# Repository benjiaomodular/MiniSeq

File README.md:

# MiniSeq
[![CC BY-SA 4.0][cc-by-sa-shield]][cc-by-sa]

Full docs on my website: https://benjiaomodular.com/post/miniseq/

This is my second time building a Baby-8 step CV sequencer since my [plexiglass Baby-8 build](https://benjiaomodular.com/post/2021-04-09-8-step-sequencer) from two years ago. This, time I added a gate output, a reset input, and a step length control.

## Schematics

## License

This work is licensed under a
[Creative Commons Attribution-ShareAlike 4.0 International License][cc-by-sa].

[![CC BY-SA 4.0][cc-by-sa-image]][cc-by-sa]

[cc-by-sa]: http://creativecommons.org/licenses/by-sa/4.0/
[cc-by-sa-image]: https://licensebuttons.net/l/by-sa/4.0/88x31.png
[cc-by-sa-shield]: https://img.shields.io/badge/License-CC%20BY--SA%204.0-lightgrey.svg

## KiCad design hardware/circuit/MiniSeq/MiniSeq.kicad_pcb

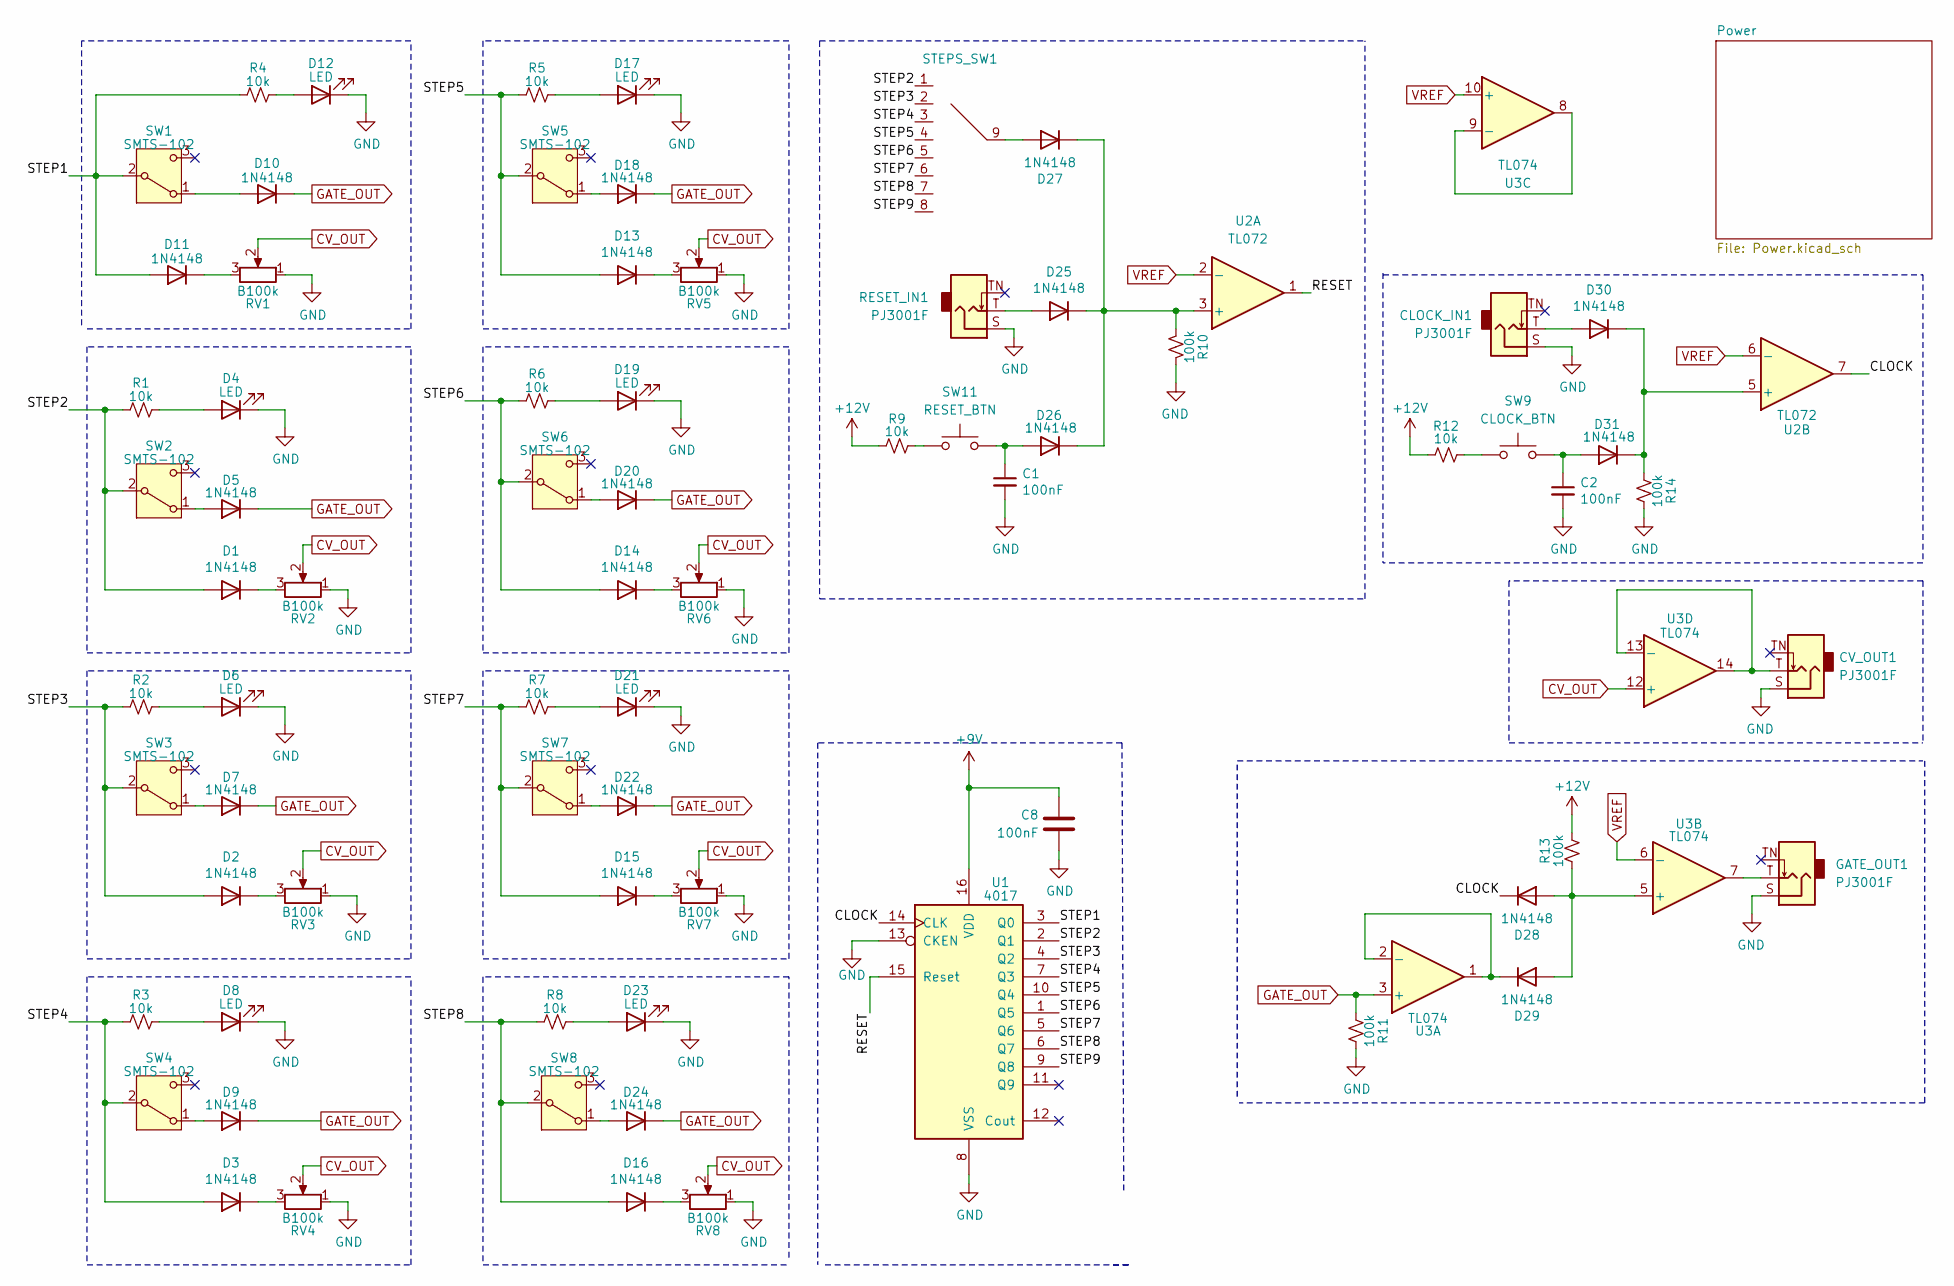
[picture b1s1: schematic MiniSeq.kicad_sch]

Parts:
C1, C2: 100nF; C_0805_2012Metric_Pad1.18x1.45mm_HandSolder; Manufacturers Part Numb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 CC0805KRX7R9BB104
C8: 100nF; C_0805_2012Metric_Pad1.18x1.45mm_HandSolder
CLOCK_IN1: PJ3001F; AudioJack_3.5mm; Manufacturers Part Numb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 PJ-3001F
CV_OUT1: PJ3001F; AudioJack_3.5mm; Manufacturers Part Numb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 PJ-3001F
D1, D2, D3, D5, D7, D9, D10, D11, D13, D14, D15, D16, D18, D20, D22, D24, D25, D26, D27, D28, D29, D30, D31: 1N4148; D_SOD-123; Manufacturers Part Numb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 1N4148WQ-7-F
D4, D6, D8, D12, D17, D19, D21, D23: LED; LED_D3.0mm
GATE_OUT1: PJ3001F; AudioJack_3.5mm; Manufacturers Part Numb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 PJ-3001F
R1, R2, R3, R4, R5, R6, R7, R8, R9, R12: 10k; R_0603_1608Metric_Pad0.98x0.95mm_HandSolder; Manufacturers Part Numb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 AC0603FR-0710KL
R10, R11, R13, R14: 100k; R_0603_1608Metric_Pad0.98x0.95mm_HandSolder; Manufacturers Part Numb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 RC0603FR-07100KL
RESET_IN1: PJ3001F; AudioJack_3.5mm; Manufacturers Part Numb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 PJ-3001F
RV1, RV2, RV3, RV4, RV5, RV6, RV7, RV8: B100k; Potentiometer_RV09; Manufacturers Part Numb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 RD901F-40-15R1-B100K
STEPS_SW1: RotarySwitch_SR16_POLE1_WAY8
SW1, SW2, SW3, SW4, SW5, SW6, SW7, SW8: SMTS-102; ToggleSwitch_SMTS-102; Manufacturers Part Numb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 SMTS-201
SW9: CLOCK_BTN; SW_Cherry_MX_1.00u_PCB
SW11: RESET_BTN; SW_Cherry_MX_1.00u_PCB
U1: 4017; SOIC-16W_5.3x10.2mm_P1.27mm; Manufacturers Part Numb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 CD40174BM96
U2: TL072; SOIC-8_3.9x4.9mm_P1.27mm; Manufacturers Part Numb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 TL072CDT
U3: TL074; SOIC-14_3.9x8.7mm_P1.27mm; Manufacturers Part Numb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 TL074ACDT

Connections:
+9V: C8.1, U1.16 (VDD); also elsewhere on the board
+12V: R9.2, R12.2, R13.1; also elsewhere on the board
/CLOCK: D28.1 (K), U1.14 (CLK), U2.7
/RESET: U1.15 (Reset), U2.1
/STEP1: D11.2 (A), R4.2, SW1.2 (B), U1.3 (Q0)
/STEP2: D1.2 (A), R1.2, STEPS_SW1.1, SW2.2 (B), U1.2 (Q1)
/STEP3: D2.2 (A), R2.2, STEPS_SW1.2, SW3.2 (B), U1.4 (Q2)
/STEP4: D3.2 (A), R3.2, STEPS_SW1.3, SW4.2 (B), U1.7 (Q3)
/STEP5: D13.2 (A), R5.2, STEPS_SW1.4, SW5.2 (B), U1.10 (Q4)
/STEP6: D14.2 (A), R6.2, STEPS_SW1.5, SW6.2 (B), U1.1 (Q5)
/STEP7: D15.2 (A), R7.2, STEPS_SW1.6, SW7.2 (B), U1.5 (Q6)
/STEP8: D16.2 (A), R8.2, STEPS_SW1.7, SW8.2 (B), U1.6 (Q7)
/STEP9: STEPS_SW1.8, U1.9 (Q8)
CV_OUT: RV1.2, RV2.2, RV3.2, RV4.2, RV5.2, RV6.2, RV7.2, RV8.2, U3.12 (+)
GATE_OUT: D5.1 (K), D7.1 (K), D9.1 (K), D10.1 (K), D18.1 (K), D20.1 (K), D22.1 (K), D24.1 (K), R11.2, U3.3 (+)
GND: C1.2, C2.2, C8.2, CLOCK_IN1.S, CV_OUT1.S, D4.1 (K), D6.1 (K), D8.1 (K), D12.1 (K), D17.1 (K), D19.1 (K), D21.1 (K), D23.1 (K), GATE_OUT1.S, R10.2, R11.1, R14.1, RESET_IN1.S, RV1.1, RV2.1, RV3.1, RV4.1, RV5.1, RV6.1, RV7.1, RV8.1, U1.8 (VSS), U1.13 (CKEN); also elsewhere on the board
unnamed: D1.1 (K), RV2.3
unnamed: D2.1 (K), RV3.3
unnamed: D3.1 (K), RV4.3
unnamed: D4.2 (A), R1.1
unnamed: D5.2 (A), SW2.1 (A)
unnamed: D6.2 (A), R2.1
unnamed: D7.2 (A), SW3.1 (A)
unnamed: D8.2 (A), R3.1
unnamed: D9.2 (A), SW4.1 (A)
unnamed: D10.2 (A), SW1.1 (A)
unnamed: D11.1 (K), RV1.3
unnamed: D12.2 (A), R4.1
unnamed: D13.1 (K), RV5.3
unnamed: D14.1 (K), RV6.3
unnamed: D15.1 (K), RV7.3
unnamed: D16.1 (K), RV8.3
unnamed: D17.2 (A), R5.1
unnamed: D18.2 (A), SW5.1 (A)
unnamed: D19.2 (A), R6.1
unnamed: D20.2 (A), SW6.1 (A)
unnamed: D21.2 (A), R7.1
unnamed: D22.2 (A), SW7.1 (A)
unnamed: D23.2 (A), R8.1
unnamed: D24.2 (A), SW8.1 (A)
unnamed: D25.2 (A), RESET_IN1.T
unnamed: D25.1 (K), D26.1 (K), D27.1 (K), R10.1, U2.3 (+)
unnamed: C1.1, D26.2 (A), SW11.2
unnamed: D27.2 (A), STEPS_SW1.9
unnamed: D28.2 (A), D29.2 (A), R13.2, U3.5 (+)
unnamed: D29.1 (K), U3.1, U3.2 (-)
unnamed: CLOCK_IN1.T, D30.2 (A)
unnamed: D30.1 (K), D31.1 (K), R14.2, U2.5 (+)
unnamed: C2.1, D31.2 (A), SW9.2
unnamed: GATE_OUT1.T, U3.7
unnamed: R9.1, SW11.1
unnamed: R12.1, SW9.1
unnamed: U3.8, U3.9 (-)
unnamed: CV_OUT1.T, U3.13 (-), U3.14
VREF: U2.2 (-), U2.6 (-), U3.6 (-), U3.10 (+); also elsewhere on the board

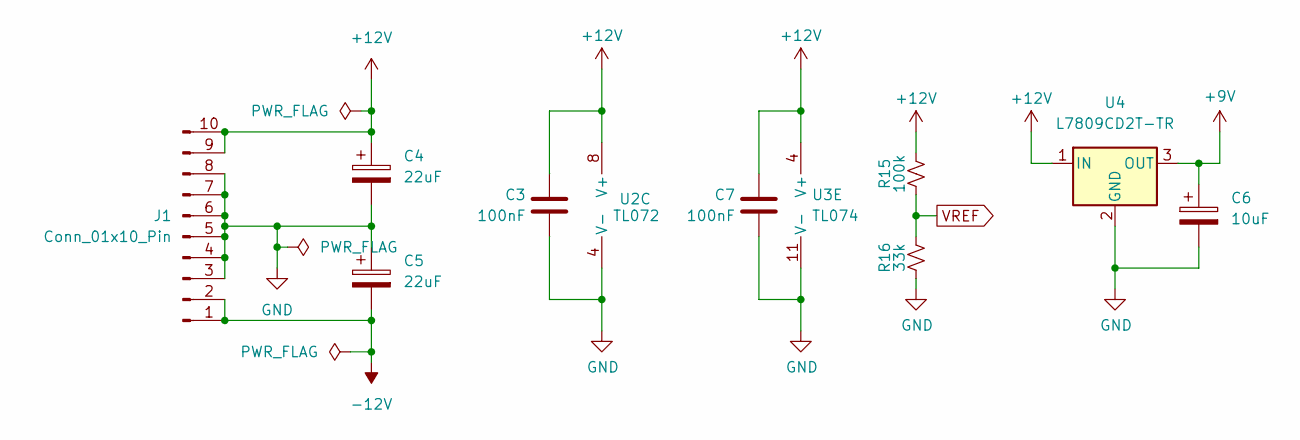
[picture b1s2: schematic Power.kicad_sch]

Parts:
C3, C7: 100nF; C_0805_2012Metric_Pad1.18x1.45mm_HandSolder
C4, C5: 22uF; CP_Elec_4x3.9
C6: 10uF; C_0805_2012Metric_Pad1.18x1.45mm_HandSolder
J1: Conn_01x10_Pin; IDC-Header_2x05_P2.54mm_Vertical
R15: 100k; R_0603_1608Metric_Pad0.98x0.95mm_HandSolder; Manufacturers Part Numb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 RC0603FR-07100KL
R16: 33k; R_0603_1608Metric_Pad0.98x0.95mm_HandSolder; Manufacturers Part Numb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 CR0603-FX-3302ELF
U2: TL072; SOIC-8_3.9x4.9mm_P1.27mm; Manufacturers Part Numb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 TL072CDT
U3: TL074; SOIC-14_3.9x8.7mm_P1.27mm; Manufacturers Part Numb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 TL074ACDT
U4: L7809CD2T-TR; TO-252-2; Manufacturers Part Numb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 L7809CD2T-TR

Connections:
+9V: C6.1, U4.3 (OUT); also elsewhere on the board
+12V: C3.1, C4.1, C7.1, J1.9, J1.10, R15.1, U2.8 (V+), U3.4 (V+), U4.1 (IN); also elsewhere on the board
-12V: C5.2, J1.1, J1.2
GND: C3.2, C4.2, C5.1, C6.2, C7.2, J1.3, J1.4, J1.5, J1.6, J1.7, J1.8, R16.2, U2.4 (V-), U3.11 (V-), U4.2 (GND); also elsewhere on the board
VREF: R15.2, R16.1; also elsewhere on the board

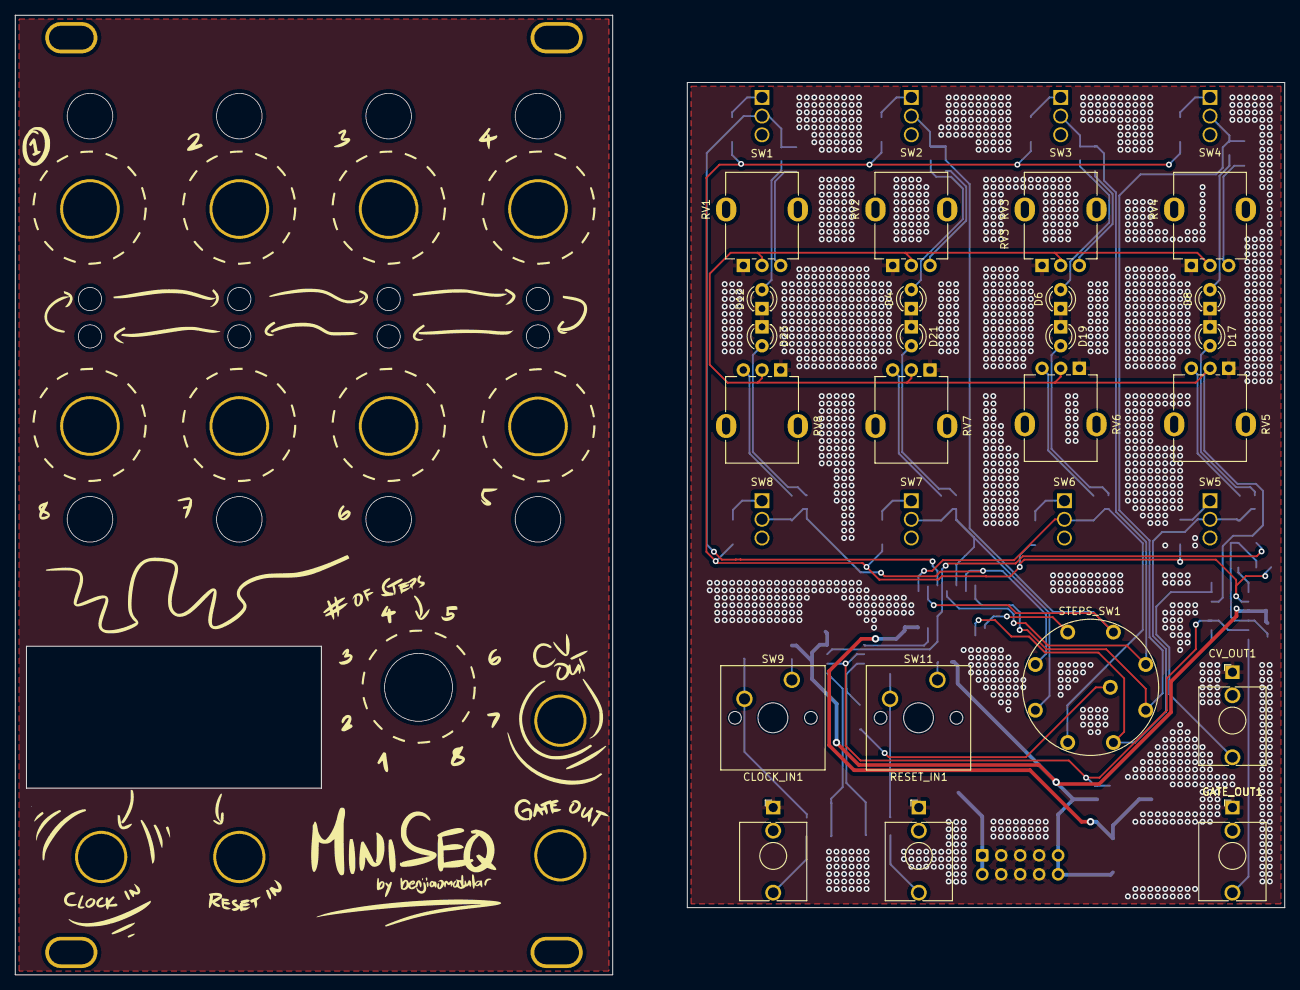
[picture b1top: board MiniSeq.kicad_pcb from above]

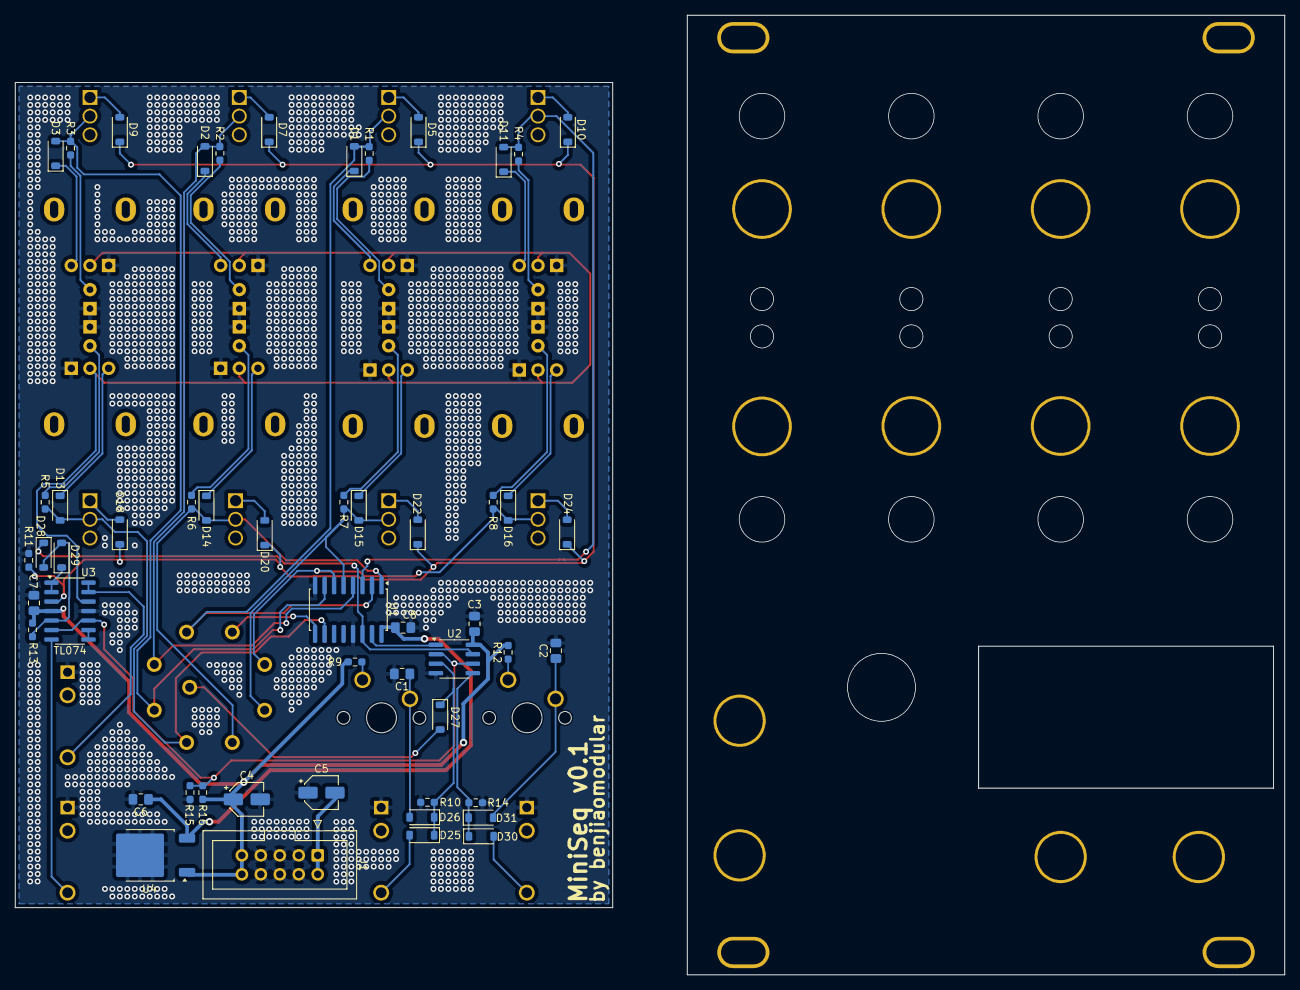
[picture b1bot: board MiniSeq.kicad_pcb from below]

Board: 2 copper layers, 80.0 x 110.5 mm, 83 parts (52 on the bottom side), 56 nets.

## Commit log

2023-08-19 Fixed schematic layout
2023-08-29 Added some docs + schematics
2023-08-29 Added link to website
2024-09-06 Reorganized files
2024-09-10 v0.1 PCBs
2024-09-11 Added copper fills to panel
2024-10-28 Updated PCBs for v0.1
